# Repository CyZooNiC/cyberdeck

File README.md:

# Cyberdeck

### 3D Models
 - Lid Plate
 - Base Plate
 - Umbilical Guide
 - Case brackets

### PCB
- SDR Controller

### Services used
 - https://blexon.com/ (Metal work)
 - https://www.tenstickers.ch/ (Stickers)

### BOM
 - Pelican case, PELI 1450 black https://www.brack.ch/peli-schutzkoffer-1450-schwarz-360008
 - Raspberry Pi 3B https://rpilocator.com/?cat=PI3
 - Toggle Switches https://secure.reichelt.com/ch/en/lever-switch-to-10-a-1x-on-on-hs-636-h2-p105645.html
 - Toggle Switch guard https://secure.reichelt.com/ch/en/safety-covers-red-schutz-20-26-p105664.html
 - INA226 Voltage Current Monitor https://www.aliexpress.com/item/1005003463006131.html
 - SD extension: https://www.aliexpress.com/item/1005001928805506.html
 - LED mount https://www.aliexpress.com/item/1005002248561990.html
 - ESP32 https://www.aliexpress.com/item/4000093420330.html
 - power connector: https://www.aliexpress.com/item/32872816780.html
 - charger: https://www.aliexpress.com/item/1005001638456602.html
 - keypad: https://www.aliexpress.com/item/4000873237364.html
 - black screws https://www.aliexpress.com/item/1005001711625966.html
 - 3S2 Battery BMS https://www.aliexpress.com/item/4000648416374.html
 - HDMI cables between top and bottom https://www.aliexpress.com/item/4001090468470.html
 - Batteries https://www.aliexpress.com/item/32324914059.html
 - USB audio https://www.aliexpress.com/item/33056020608.html
 - USB hub https://www.aliexpress.com/item/4000292920801.html
 - SMA extnesion https://www.aliexpress.com/item/4000245307369.html
 - Knobs https://www.aliexpress.com/item/32608693397.html
 - Step down modules https://www.aliexpress.com/item/32706909050.html
 - Rotary encoder https://www.aliexpress.com/item/32873198060.html
 - DIN clips https://www.aliexpress.com/item/1005001834824551.html
 - DIN bridge https://www.aliexpress.com/item/1005001834788898.html
 - OLED display https://www.aliexpress.com/item/33027484504.html
 - Pannel buttons https://www.aliexpress.com/item/1005001732343587.html
 - gigabit switch https://www.aliexpress.com/item/32991083909.html
 - RTL SDR https://www.aliexpress.com/item/1005001271827620.html
 - DIN rail https://www.aliexpress.com/item/4000126680453.html
 - jack dust covers https://www.aliexpress.com/item/4000484462480.html
 - pannel ports https://www.aliexpress.com/item/4000102342780.html
 - LCD 11.6 -https://www.aliexpress.com/item/4001050343035.html
 - keyboard https://www.aliexpress.com/item/4001224586963.html
 - water proof USB https://www.aliexpress.com/item/32902706764.html
 - water proof network https://www.aliexpress.com/item/32856098897.html
 - Umbilical 180mm https://www.aliexpress.com/item/1005001568585310.html

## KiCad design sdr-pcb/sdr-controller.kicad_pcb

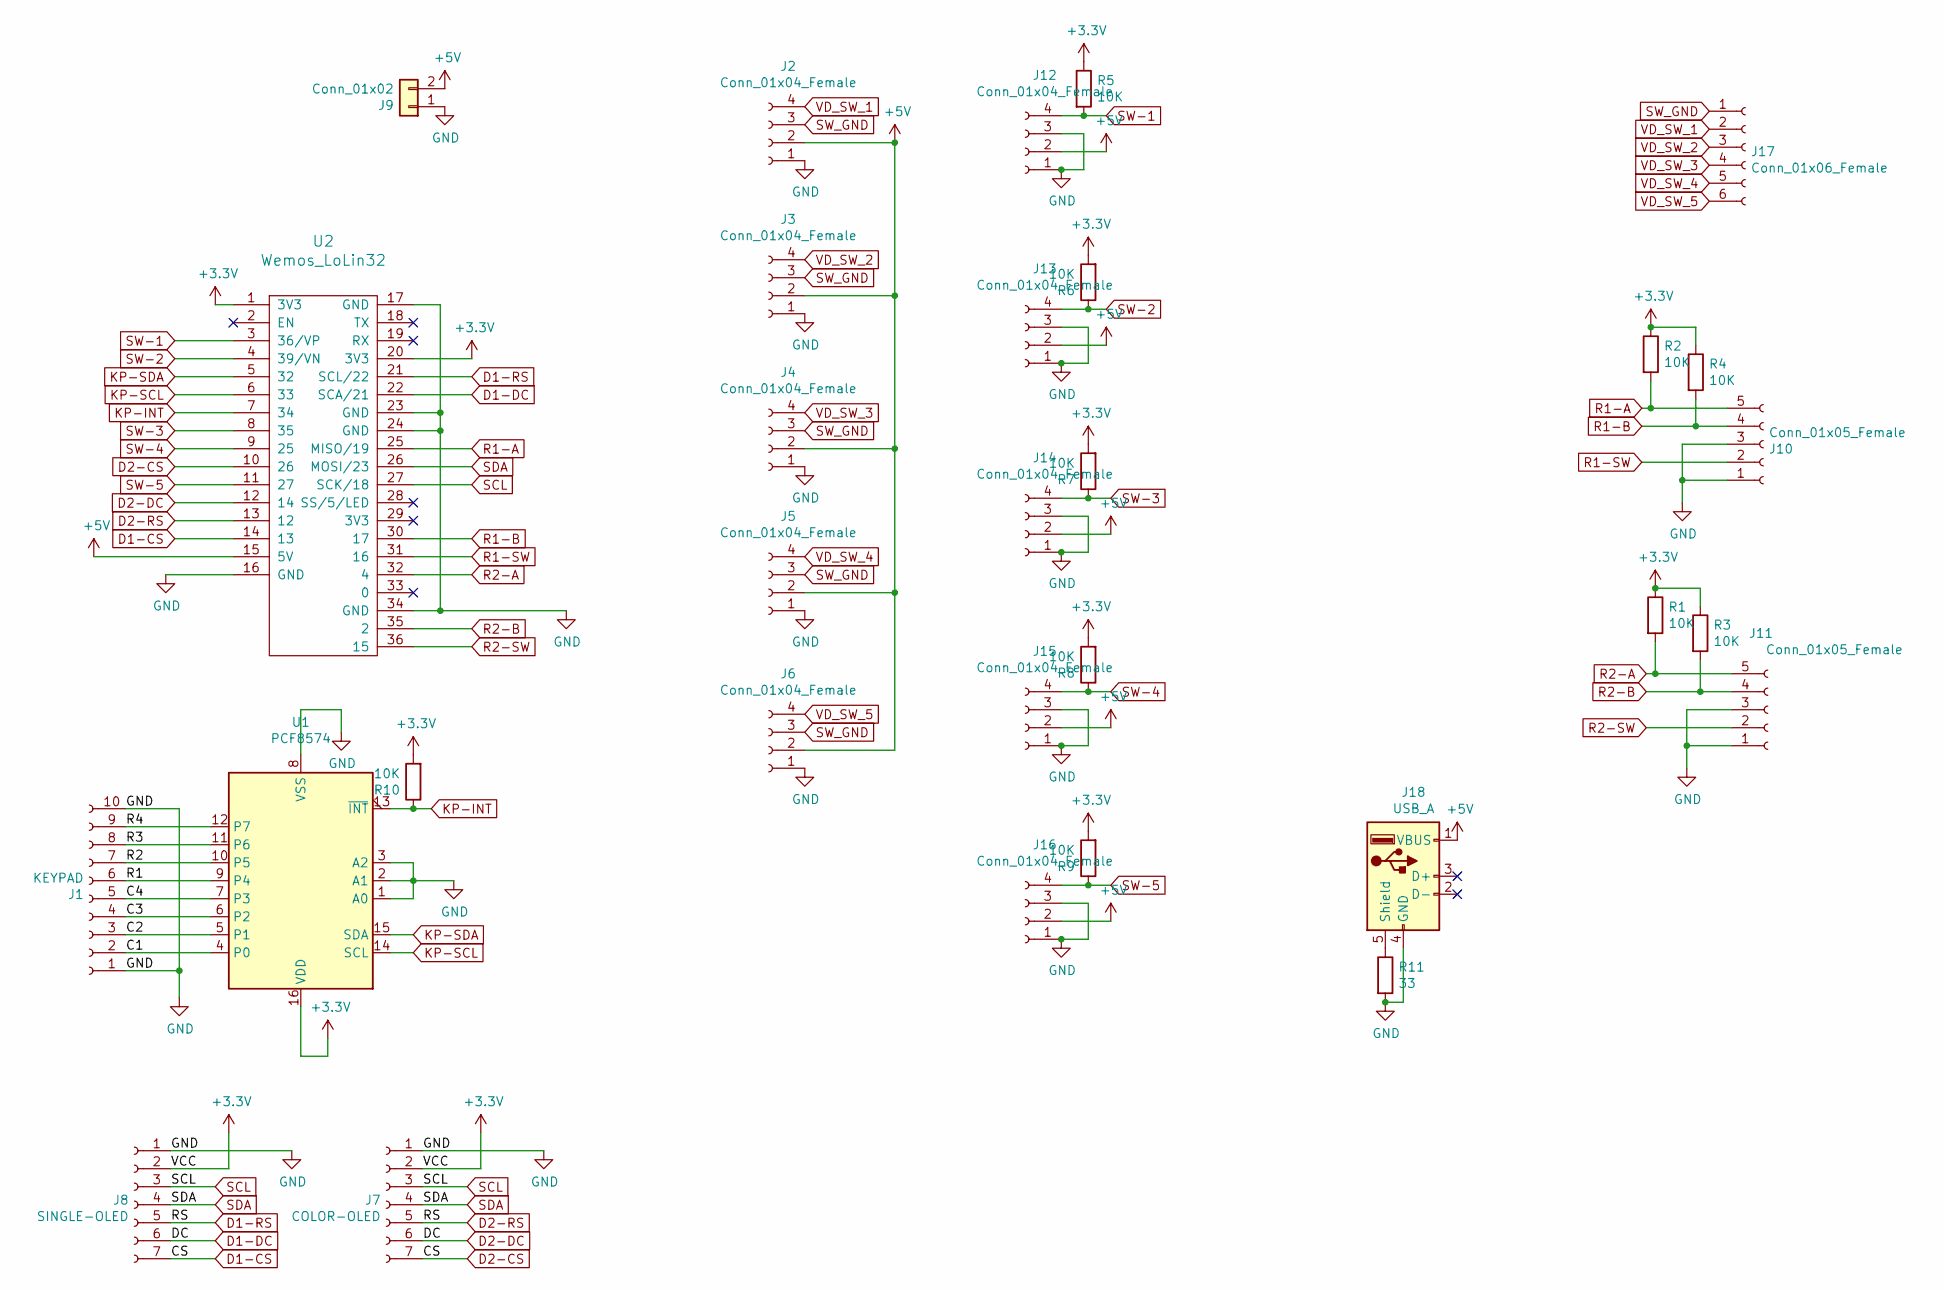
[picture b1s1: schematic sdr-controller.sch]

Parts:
J1: KEYPAD; Pin_Header_Straight_1x10_Pitch2.54mm
J2, J3, J4, J5, J6, J12, J13, J14, J15, J16: Conn_01x04_Female; Molex_KK-6410-04_04x2.54mm_Straight
J7: COLOR-OLED; Molex_KK-6410-07_07x2.54mm_Straight
J8: SINGLE-OLED; Molex_KK-6410-07_07x2.54mm_Straight
J9: Conn_01x02; Molex_KK-6410-02_02x2.54mm_Straight
J10, J11: Conn_01x05_Female; Molex_KK-6410-05_05x2.54mm_Straight
J17: Conn_01x06_Female; Molex_KK-6410-06_06x2.54mm_Straight
J18: USB_A; USB-Module-Micro
R1, R2, R3, R4, R5, R6, R7, R8, R9, R10: 10K; 1206
R11: 33; 1206
U1: PCF8574; DIP-16_W7.62mm
U2: Wemos_LoLin32; LoLin_32_Board

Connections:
+3V3: J7.2, J8.2, R1.1, R2.1, R3.1, R4.1, R5.1, R6.2, R7.2, R8.2, R9.2, R10.2, U1.16 (VDD), U2.1 (3V3), U2.20 (3V3)
+5V: J2.2, J3.2, J4.2, J5.2, J6.2, J9.2, J12.2, J13.2, J14.2, J15.2, J16.2, J18.1 (VBUS), U2.15 (5V)
/C1: J1.2, U1.4 (P0)
/C2: J1.3, U1.5 (P1)
/C3: J1.4, U1.6 (P2)
/C4: J1.5, U1.7 (P3)
/R1: J1.6, U1.9 (P4)
/R2: J1.7, U1.10 (P5)
/R3: J1.8, U1.11 (P6)
/R4: J1.9, U1.12 (P7)
D1-CS: J7.7, J8.7, U2.10 (26), U2.14 (13)
D1-DC: J7.6, J8.6, U2.12 (14), U2.22 (SCA/21)
D1-RS: J7.5, J8.5, U2.13 (12), U2.21 (SCL/22)
GND: J1.1, J1.10, J2.1, J3.1, J4.1, J5.1, J6.1, J7.1, J8.1, J9.1, J10.1, J10.3, J11.1, J11.3, J12.1, J12.3, J13.1, J13.3, J14.1, J14.3, J15.1, J15.3, J16.1, J16.3, J18.4 (GND), R11.2, U1.1 (A0), U1.2 (A1), U1.3 (A2), U1.8 (VSS), U2.16 (GND), U2.17 (GND), U2.23 (GND), U2.24 (GND), U2.34 (GND)
KP-INT: R10.1, U1.13 (~INT~), U2.7 (34)
KP-SCL: U1.14 (SCL), U2.6 (33)
KP-SDA: U1.15 (SDA), U2.5 (32)
unnamed: J18.5 (Shield), R11.1
R1-A: J10.5, R2.2, U2.25 (MISO/19)
R1-B: J10.4, R4.2, U2.30 (17)
R1-SW: J10.2, U2.31 (16)
R2-A: J11.5, R1.2, U2.32 (4)
R2-B: J11.4, R3.2, U2.35 (2)
R2-SW: J11.2, U2.36 (15)
SCL: J7.3, J8.3, U2.27 (SCK/18)
SDA: J7.4, J8.4, U2.26 (MOSI/23)
SW-1: J12.4, R5.2, U2.3 (36/VP)
SW-2: J13.4, R6.1, U2.4 (39/VN)
SW-3: J14.4, R7.1, U2.8 (35)
SW-4: J15.4, R8.1, U2.9 (25)
SW-5: J16.4, R9.1, U2.11 (27)
SW_GND: J2.3, J3.3, J4.3, J5.3, J6.3, J17.1
VD_SW_1: J2.4, J17.2
VD_SW_2: J3.4, J17.3
VD_SW_3: J4.4, J17.4
VD_SW_4: J5.4, J17.5
VD_SW_5: J6.4, J17.6

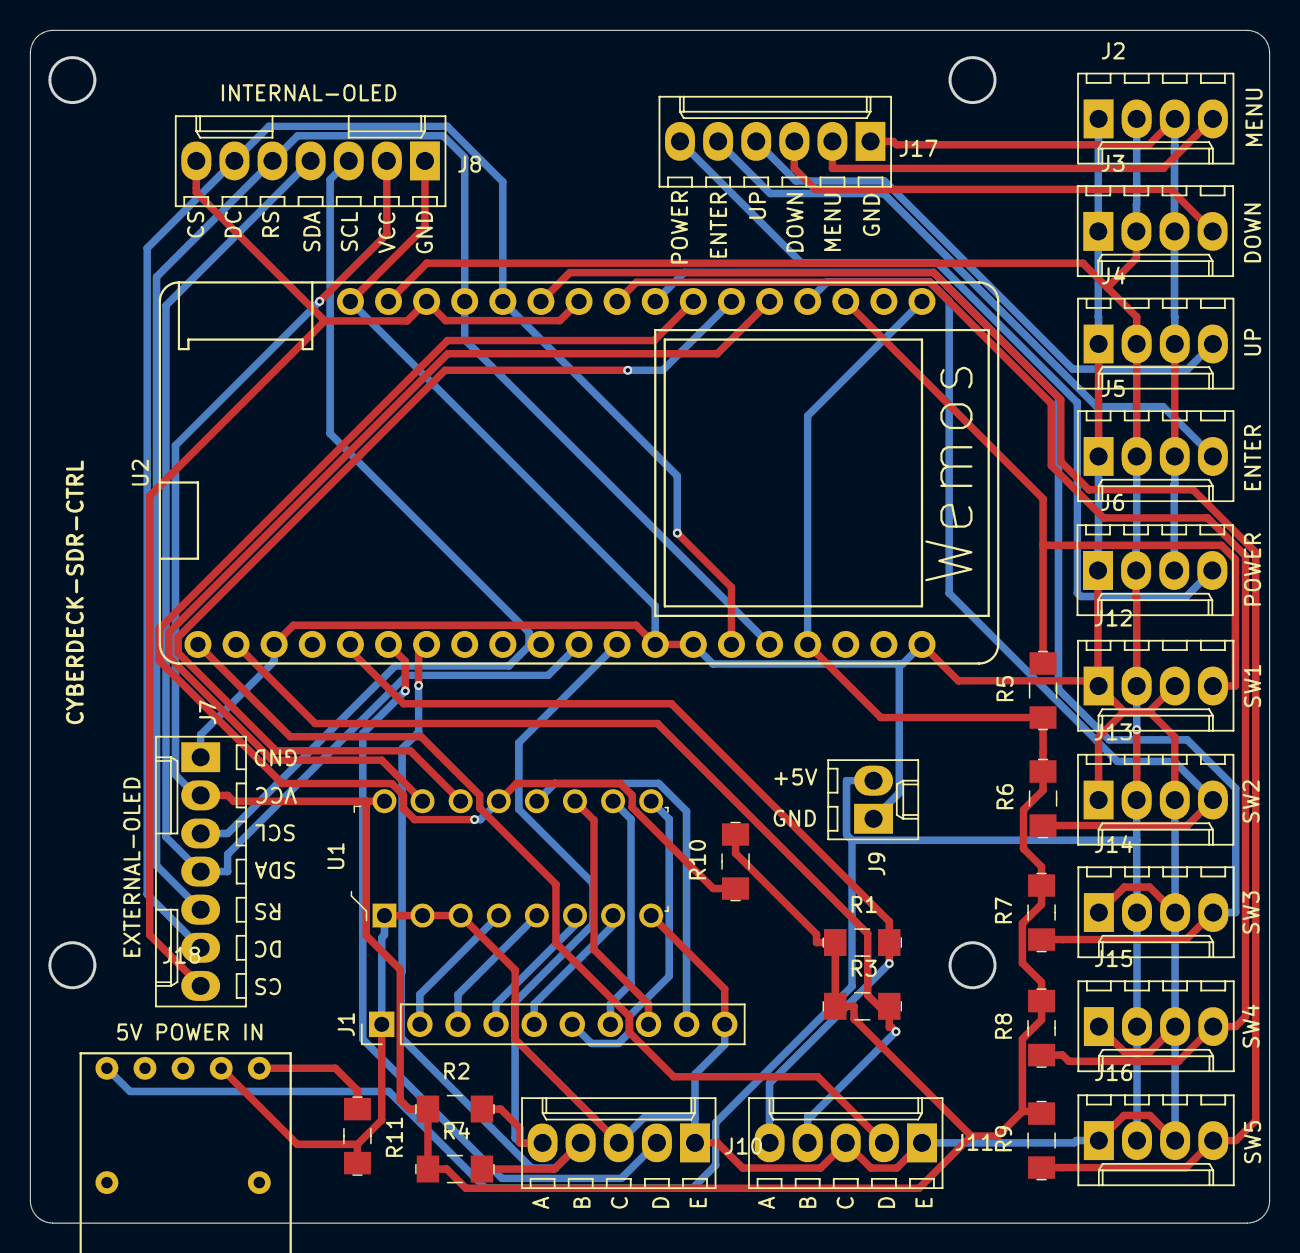
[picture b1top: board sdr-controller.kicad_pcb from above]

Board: 2 copper layers, 82.5 x 79.4 mm, 31 parts (0 on the bottom side), 37 nets.

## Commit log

2022-02-05 Readme
2022-02-05 3d models
2022-02-05 Photos
2022-02-05 Artwork
2022-02-05 PCB photos
2022-02-08 more photos
2022-03-13 s/Ambilical/Umbilical/g
2022-03-13 mv 3dmodels/Ambilical_guide 3dmodels/Umbilical_guide
2022-04-10 doc: Added more links to readme
2022-08-10 Update README.md
    Added html cables
2023-12-30 Added AGPL license
